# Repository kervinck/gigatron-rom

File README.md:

Software for Gigatron ROM
=========================

Important files
===============
```
gigatron-rom
 +--- LICENSE                   2-Clause BSD License
 +--- Makefile                  Marcel's Makefile
 +--- Core/                     Gigatron kernel and build tools
 |     +--- dev.asm.py          Development ROM (type 'make' to build):
 |     |                        Video/audio/io/kernel loops and cold storage
 |     |                        for applications and data ("kernel + ROM disk")
 |     +--- ROMv6.asm.py        Source for release ROM v6 (most recent release)
 |     `--- compilegcl.py       Stand-alone GCL to vCPU compiler (GT1 files)
 +--- interface.json            Formal bindings interface to ROM for programs
 +--- Apps/                     Built-in and example applications (GCL and GT1)
 |     +--- Blinky/Blinky.gcl   Very simple GCL program
 |     `--- HelloWorld/         Program that draws "Hello world" on screen
 +--- BASIC/                    Example BASIC programs
 +--- Utils/
 |     +--- BabelFish/          Generic Arduino sketch for talking with Gigatron
 |     +--- gt1dump.py          Dump or disassemble GT1 files
 |     +--- lcc/                LCC compiler with vCPU backend (NOT YET STABLE)
 |     `--- sendFile.py         Send GT1 or BASIC file from laptop/PC
 +--- Libs/                     C libraries for Gigatron programs
 |     `--- Example.c           Example C program
 +--- Docs/
 |     +--- GCL-language.txt    Gigatron Control Language and vCPU explanation
 |     +--- GT1-files.txt       vCPU object file format and ROM versioning
 |     +--- gtemu.c             Instruction set definition (as executable code)
 |     +--- vCPU-summary.txt    Overview of 16-bit virtual CPU instruction set
 |     `--- ...                 All on video, audio, native code, versioning...
 `--- Contrib/                  Contributions outside the kit's ROM and tooling:
       +--- at67/               BASIC compiler, emulator, 8-bit/16-bit
       |                        assembler/disassembler, debugger, MIDI music,
       |                        demos and games
       +--- Crouze/             TinyBASIC scripts (including graphclock.gtb)
       +--- Cwiiis/             Gigatris game
       +--- delpozzo/           VideoPoker game; Tools (CustomFish, sendFile)
       +--- dhkolf/             Fast emulator; Demos (SprPaint, PianoBeep,...)
       +--- docvolt/            Implementation on Sipeed Tang Nano 9K FPGA board
       +--- flok99/             Simple (and slow) visualizer using SDL2
       +--- gigawalt/           Walter's script
       +--- kervinck/           Ramblings (all work in progress)
       +--- makerspace48/       C examples, Prime.c and ASCII-mandelbrot.c
       +--- PhilThomas/         Javascript-based Gigatron emulator
       +--- pkupper/            Pluggy Reloaded's Babelfish (to be merged back)
       +--- tbraun-de/          Gigatron Mac; Python port of gtemu.c; maze.gt1
       +--- xopr/               NetTerm: Terminal program for SPI interface
       `--- xxxbxxx/            Bricks game; RPi port of BabelFish; frogstroll
```

Files generated by ROMv6.asm.py
===============================

See `Makefile` for how to make these.
```
ROMv6.lst                       Generated listing with disassembly, labels,
                                comments and source (large!)
ROMv6.rom                       ROM file for 27C1024 (PCB versions)
```

Memory map (RAM)
================
```
              0 1          53 54     127 128 129         (vSP)       255
             +-+-------------+-----------+-+-------------+--------------+
page 0       |0| System vars | User vars |1| User vars <-| Stack/Loader |
             +-+-------------+-----------+-+------+------+--+-----------+
page 1       | Video table                        | vReset  | Channel 1 |
             +------------------------------------+---------+-----------+ ---
page 2       |0                                239 240   249| Channel 2 |  ^
             |                                              +-----------+  |  Also see
page 3       |                                              | Channel 3 |  |  channelMask
             |                                              +-----------+  |
page 4       |            User vCPU code and/or data        | Channel 4 |  v
             |                                              +-----------+ ---
page 5-6     |                                               250     255|
             |                                                          |
             |                                               <- C stack |
             +----------------------------------------------------------+
page 7       | Sound tables                                             |
             +--------------------------------+-------------------------+
page 8-127   |0                            159|160                   255|
             | 120 lines of 160 pixels        |  Extra space for user   |
             | Default video memory           |  code and/or data       |
             =                                =                         =
             |                                |                         |
             +--------------------------------+-------------------------+
page 128-255 | - Gigatron 32K: mirrors pages 0-127                      |
             | - Gigatron 64K: additional 32KB or RAM                   |
	     | - Gigatron with RAM&IO expansion: banked memory          |
	     |   | bank 0       mirrors page 0-127                      |
             |   | banks 1,2.3  three additional banks of 32K RAM       |
             +----------------------------------------------------------+
              0                                                      255

[Note: In the next section, names in parentheses refer to *internal*
variables that are subject to change between ROM versions. See for a
more detailed explanation on compatibility the file Docs/GT1-files.txt]

Address   Name          Description
--------- ------------- -----------
0000      zeroConst     Constant value 0 (for arithmetic carry)
0001      memSize       Number of RAM pages detected at hard reset (64kB=0)
0002      (channel)     Sound channel update on current scanline
0003      (sample)      Accumulator for synthesizing next sound sample
0004      (reserved)    Reserved (Video extensions? MMU? v8808? ...?)
0005      (vCpuSelect)  Entry page of active interpreter (offset fixed to 255)
0006-0008 entropy       Randomness from SRAM boot and input, updated each frame
0009      videoY        Counts up from 0 to 238 in steps of 2 (odd in vBlank)
000a      (frameX)      Starting byte within page for pixel burst
000b      (frameY)      Page of current pixel row (updated by videoA)
000c      (nextVideo)   Jump offset to scan line handler (videoA, B, C...)
000d      (videoModeD)  Handler for every 4th line (pixel burst or vCPU)
000e      frameCount    Continuous video frame counter
000f      serialRaw     New raw serial read
0010      (serialLast)  Previous serial read (used for edge detection)
0011      buttonState   Edge-triggered and resettable input bits
0012      (resetTimer)  After 2 seconds of holding 'Start', do a soft reset
0013      (xout)        Memory cache for XOUT register
0014      xoutMask      The blinkenlights and sound on/off state
0015      (vTicks)      Remaining interpreter ticks (=units of 2 CPU cycles)
0016-0017 vPC           Interpreter program counter, points into RAM
0018-0019 vAC           Interpreter accumulator, 16-bits
0018      v6502_A       [v6502] Accumulator
0019      (v6502_BI)    [v6502] B Input Register (used by SBC)
001a-001b vLR           Return address, for returning after CALL
001a-001b v6502_PC      [v6502] Program Counter
001c      vSP           Stack pointer
001c      (v6502_S)     [v6502] Stack Pointer (kept as "S+1")
001d      (vTmp)        Scratch storage location for vCPU and v6502
001e      (vReturn)     Return address (L) from vCPU into the loop (H is fixed)
001f      (videoModeB)  ROMv2: Handler for every 2nd line (pixel burst or vCPU)
0020      (videoModeC)  ROMv2: Handler for every 3rd line (pixel burst or vCPU)
0021      romType       ROM v1:$1c v2:$20 v3:$28 v4:$38 v5a:0x40 v6:0x48 DEV:$f8
0021      channelMask   Low bits set active channels (x011->4, x001->2, x000->1)
0022-0023 sysFn         Address for SYS function call
0024-002b sysArgs       Arguments for SYS functions
0024      (v6502_ADL)   [v6502] Low Address Register
0025      (v6502_ADH)   [v6502] High Address Register
0026      (v6502_IR)    [v6502] Instruction Register
0027-0029 (v6502_P)     [v6502] Processor Status Register
002a      v6502_X       [v6502] Index Register X
002b      v6502_Y       [v6502] Index Register Y
002c      soundTimer    Countdown timer for playing sound
002d      (ledTimer)    Number of frames until next LED change
002e      ledState      Current LED state machine value (branch offset)
002f      ledTempo      Next value for ledTimer after LED state change
0030-007f userVars      Program variables (ROM<=v4)
0030-0035 (vIrqSave)    (v5+) vIRQ saved registers
0036-007f userVars_v5   Program variables (ROM v5)
0036-007f userVars_v6   Program variables (ROM v6)
0080      oneConst      Constant value 1 (for arithmetic carry)
0081-.... userVars2     More space for program variables
....-00ff <stack>       Call and value stack for vCPU (also used by ROM loader)
0100-01ef videoTable    Video indirection table (Y0,dX0,Y1,dX1,Y2,...,dX119)
01f0-01f5 vReset        vCPU routine to load and start Reset sequence
01f6-01f7 vIRQ_v5       (v5) Pointer to vCPU vIRQ handler
01f8      ctrlBits_v5   (v5) RAM and IO expansion control word
01f9      videoTop_v5   (v5) Blank top of screen. Must be even in [0..238].
01fa      wavA[1]       Sound channel 1: Waveform modulation with `adda'
01fb      wavX[1]       ...............: Waveform modulation with `xora'
01fc      keyL[1]       ...............: Frequency low 7 bits (bit7 == 0)
01fd      keyH[1]       ...............: Frequency high 8 bits
01fe      oscL[1]       ...............: Phase low 7 bits
01ff      oscH[1]       ...............: Phase high 8 bits
0200-02f9 userCode      vCPU code/data (default start of user code)
02fa      wavA[2]       Sound channel 2: Waveform modulation with `adda'
02fb      wavX[2]       ...............: Waveform modulation with `xora'
02fc      keyL[2]       ...............: Frequency low 7 bits (bit7 == 0)
02fd      keyH[2]       ...............: Frequency high 8 bits
02fe      oscL[2]       ...............: Phase low 7 bits
02ff      oscH[2]       ...............: Phase high 8 bits
0300-03f9 -             vCPU code/data
03fa      wavA[3]       Sound channel 3: Waveform modulation with `adda'
03fb      wavX[3]       ...............: Waveform modulation with `xora'
03fc      keyL[3]       ...............: Frequency low 7 bits (bit7 == 0)
03fd      keyH[3]       ...............: Frequency high 8 bits
03fe      oscL[3]       ...............: Phase low 7 bits
03ff      oscH[3]       ...............: Phase high 8 bits
0400-04f9 -             vCPU code/data
04fa      wavA[4]       Sound channel 4: Waveform modulation with `adda'
04fb      wavX[4]       ...............: Waveform modulation with `xora'
04fc      keyL[4]       ...............: Frequency low 7 bits (bit7 == 0)
04fd      keyH[4]       ...............: Frequency high 8 bits
04fe      oscL[4]       ...............: Phase low 7 bits
04ff      oscH[4]       ...............: Phase high 8 bits
0500-05ff -             vCPU code/data
0600-06ff -             vCPU code/data
0700-07ff soundTable    Interlaced waveforms (metal, triangle, pulse, sawtooth)
0800-7fff screenMemory  Default pages for screen memory
0800-089f -             Pixel line 0
08a0-08ff -             vCPU code/data
.........
7f00-7f9f -             Pixel line 119
7fa0-7fff -             vCPU code/data
--------- ------------- -----------
```

Memory map (ROM)
================
```
             +----------------------------------------------------------+  ---
$0000        | Boot and reset sequences                                 |   ^
             +----------------------------------------------------------+   |
$0100        | Video and audio loop (vertical blank lines)              |   |
             |                                                          |   |
$0200        | Video and audio loop (visible lines)                     |   |
             +----------------------------------------------------------+   |
$0300        | vCPU interpreter loop (primary page)                     |   |
             |                                                          |   |
$0400        | vCPU extended instructions (and some SYS functions)      |   |
             +----------------------------------------------------------+   |
$0500        | Shift tables                                             |   |
             |                                                          |   |  Core system
$0600        | SYS functions (LSRW and others)                          |   |  Kernel and drivers
             +----------------------------------------------------------+   |
$0700        | Font table (ASCII 32..81)                                |   |
             |                                                          |   |
$0800        | Font table (ASCII 82..126 and symbols 127-131)           |   |
             |                                                          |   |
$0900        | Notes table (C-0..A#7)                                   |   |
             |                                                          |   |
$0a00        | Inversion table                                          |   |
             +----------------------------------------------------------+   |
$0b00        | SYS functions (SendSerial, Sprites, SPI, ...)            |   |
             |                                                          |   |
$0d80-$11ff  | v6502 secondary interpreter                              |   |
             |                                                          |   |
$1200-$1241  | More proceesing during vertical blank lines              |   |
             |                                                          |   |
$1242-$14ff  | More SYS functions                                       |   |
             |                                                          |   v
             +==========================================================+  ---
             |                                                          |   ^
             | ROM tables: Embedded high-resolution images (packed)     |   |
             |                                                          |   |  Applications /
$1500-$ffff  | Include files: application-specific SYS functions        |   |  cold storage
             |                                                          |   |
             | ROM files: Embedded vCPU/v6502 applications (serialized) |   |
             |                                                          |   v
             +----------------------------------------------------------+  ---
              0                                                      255
```

SYS functions (ROM)
===================

```
Available since ROM v1:

00ad    SYS_Exec_88                     Load serialized vCPU code from ROM and execute
04a7    SYS_Random_34                   Get random number and update entropy
0600    SYS_LSRW1_48                    Shift right 1 bit
0619    SYS_LSRW2_52                    Shift right 2 bits
0636    SYS_LSRW3_52                    Shift right 3 bits
0652    SYS_LSRW4_50                    Shift right 4 bits
066d    SYS_LSRW5_50                    Shift right 5 bits
0687    SYS_LSRW6_48                    Shift right 6 bits
04b9    SYS_LSRW7_30                    Shift right 7 bits
04c6    SYS_LSRW8_24                    Shift right 8 bits
06a0    SYS_LSLW4_46                    Shift left 4 bits
04cd    SYS_LSLW8_24                    Shift left 8 bits
04e1    SYS_VDrawBits_134               Draw 8 vertical pixels
06c0    SYS_Unpack_56                   Unpack 3 bytes into 4 pixels
04d4    SYS_Draw4_30                    Copy 4 pixels to screen memory
00f4    SYS_Out_22                      Write byte to hardware OUT register
00f9    SYS_In_24                       Read byte from hardware IN port

Added in ROM v2:

0b00    SYS_SetMode_v2_80               Set video mode 0..3
0b03    SYS_SetMemory_v2_54             Set 1..256 bytes of memory to value

Added in ROM v3:

0b06    SYS_SendSerial1_v3_80           Send data out over game controller port
0c00    SYS_Sprite6_v3_64               Draw sprite of 6 pixels wide and N pixels high
0c40    SYS_Sprite6x_v3_64              Draw sprite mirrored in X direction
0c80    SYS_Sprite6y_v3_64              Draw sprite upside down
0cc0    SYS_Sprite6xy_v3_64             Draw sprite mirrored and upside down

Added in ROM v4:

0b09    SYS_ExpanderControl_v4_40       Set register in I/O and RAM expander
0b0c    SYS_Run6502_v4_80               Execute MOS 6502 code until BRK
0b0f    SYS_ResetWaveforms_v4_50        Setup sound tables in page 7
0b12    SYS_ShuffleNoise_v4_46          Shuffle noise table in page 7
0b15    SYS_SpiExchangeBytes_v4_134     Send and receive bytes

Added in ROM v5a:

00ef    SYS_ReadRomDir_v5_80            Navigate ROM directory

Added in ROM v6:

009e    SYS_Multiply_s16_v6_66          16 bits multiplication (from at67)
00a1    SYS_Divide_s16_v6_80            15 bits unsigned division (from at67)
00e6    SYS_ScanMemory_v6_50            Search byte in memory region
00e9    SYS_CopyMemory_v6_80            Copy memory region
00ec    SYS_CopyMemoryExt_v6_100        Copy memory across RAM extension banks
0b18    SYS_ReceiveSerial1_v6_32        Receive byte on input port (for the loader)

```

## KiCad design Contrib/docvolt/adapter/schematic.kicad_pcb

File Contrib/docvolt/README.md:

# Gigatron Running on FPGA
Verilog implementation of the Gigatron for the Tang Nano 9K FPGA board.

## Installation
Download and install the free *GOWIN EDA software* here: https://www.gowinsemi.com/en/support/download_eda (Prior registration is required)
The programmer is appropriate if you just want to flash the Tang Nano without making changes to the code. If you want to make changes, Gowin EDA is needed. The education version is sufficient there.

Notes: 
- The non-education version of the programs require a license. 
- There is an issue with Gowin Programmer V1.9.9.03. Use V1.9.9.02 instead. Later versions might also work.

## Flashing the Tang Nano
- Double-click the cell below "Operation" to open the Device configuration dialog.
- Select the bitstream file "gigatron.fs" and the flash initialization file "fpga_games.fi"

- Then save and click the "Configure/Program" button to write it all to the FPGA.

## Adapter Board
A VGA monitor, game controller and audio can be connected through the adapter board.

Find schematics and Gerber files of the adapter board here: [Schematic](schematic)

## Building the User Flash File From Source
The user flash file is basically the Gigatron's rom file, but in a format that's understood by the Gowin Programmer (ending: .fi). Unlike the gigatron's rom file which has a maximum size of 64K, the maximm size of the user flash file is 38K. This is due to the size of the embedded user flash of 608 KBit = 38K 16-bit words.
If you want to (re)build it, type "make games.rom" in a Linux command shell. I was using WSL/Ubuntu under Windows. Cygwin, MinGW, MSYS etc. do not work (at least not for me) 

## Youtube Video
More details in the video.

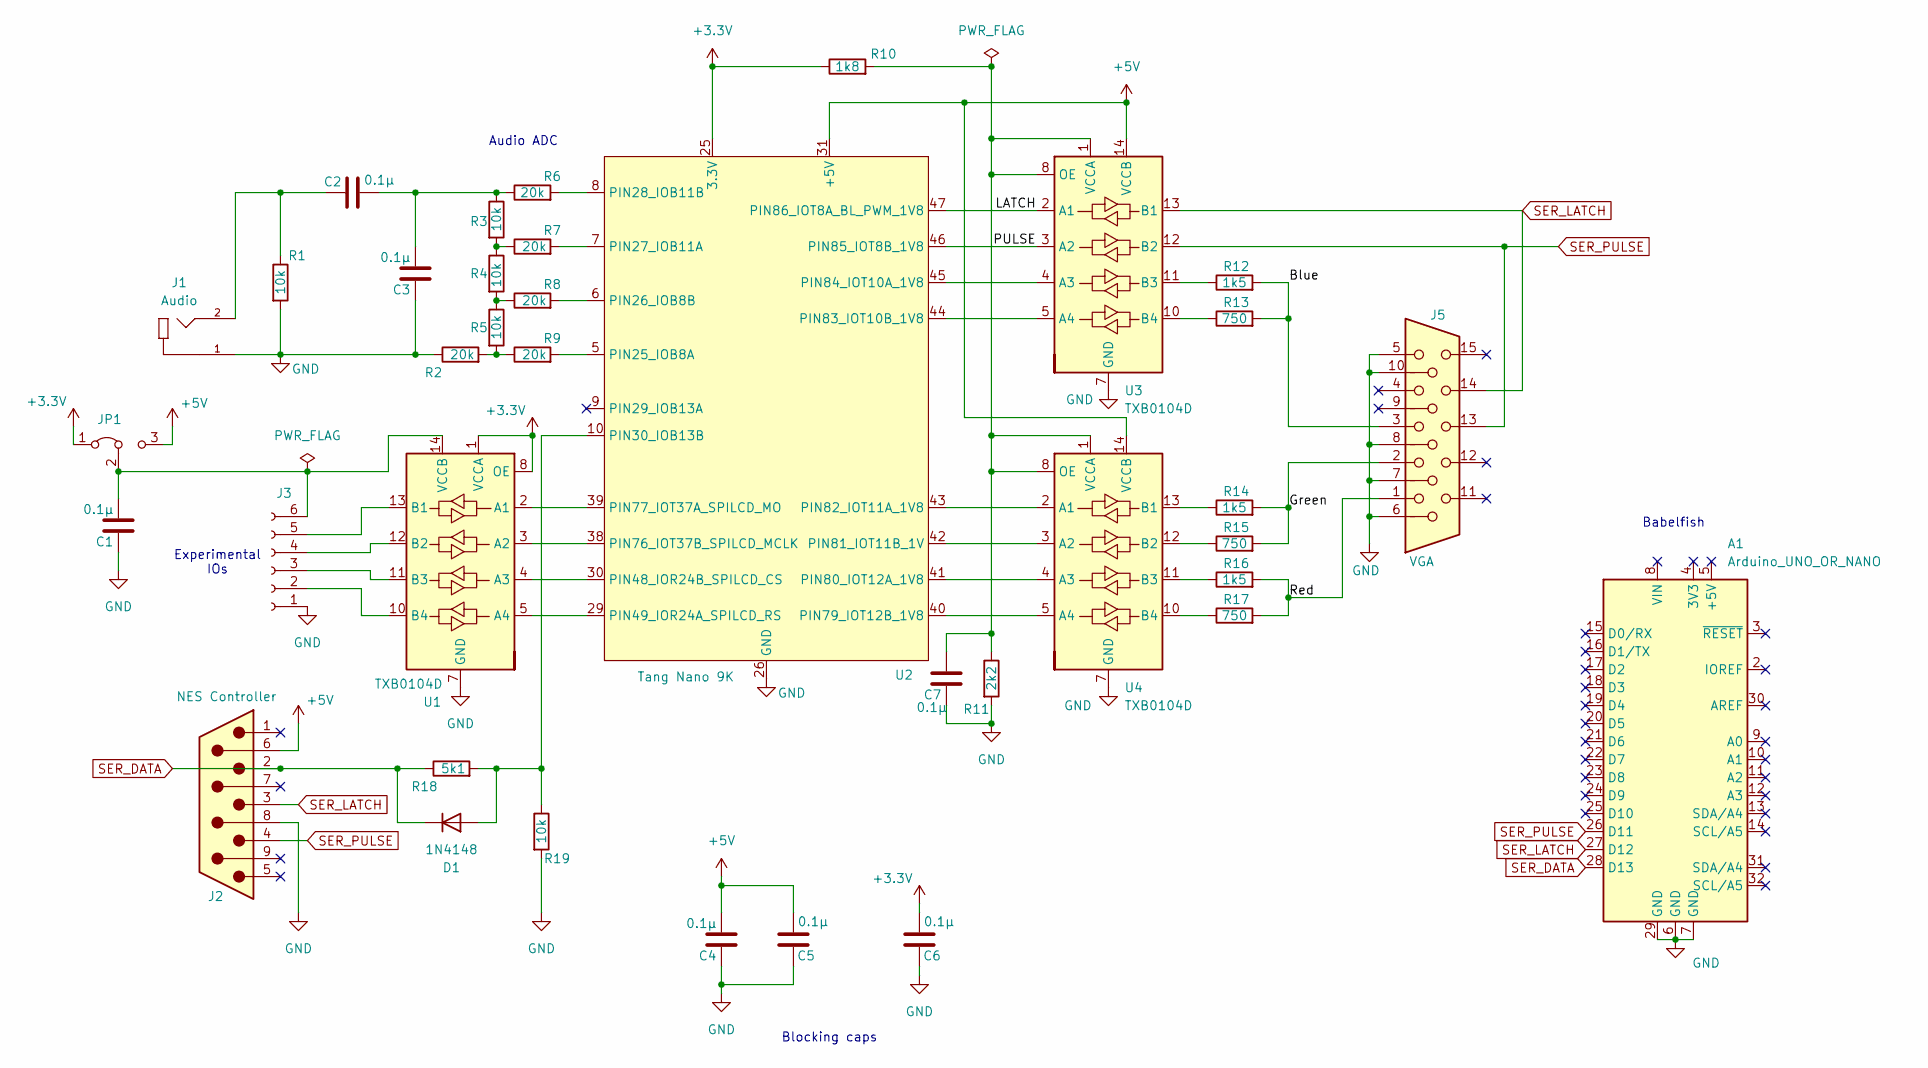
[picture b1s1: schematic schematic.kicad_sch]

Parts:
A1: Arduino_UNO_OR_NANO; Arduino_UNO_R3
C1, C2, C3, C4, C7: 0.1µ; C_Disc_D5.0mm_W2.5mm_P2.50mm
C5, C6: 0.1µ; C_1206_3216Metric_Pad1.33x1.80mm_HandSolder
D1: 1N4148; D_DO-35_SOD27_P7.62mm_Horizontal
J1: Audio; CUI_RCJ-041
J2: NES Controller; AMPHENOL_L717SDE09PA4CH4R
J3: Conn_01x06_Socket; PinSocket_1x06_P2.54mm_Vertical
J5: VGA; AMPHENOL_L77HDE15SD1CH4R
JP1: Jumper_3_Bridged12; Jumper
R1, R3, R4, R5, R19: 10k; R_Axial_DIN0207_L6.3mm_D2.5mm_P7.62mm_Horizontal
R2, R6, R7, R8, R9: 20k; R_Axial_DIN0207_L6.3mm_D2.5mm_P7.62mm_Horizontal
R10: 1k8; R_Axial_DIN0207_L6.3mm_D2.5mm_P7.62mm_Horizontal
R11: 2k2; R_Axial_DIN0207_L6.3mm_D2.5mm_P7.62mm_Horizontal
R12, R14, R16: 1k5; R_Axial_DIN0207_L6.3mm_D2.5mm_P7.62mm_Horizontal
R13, R15, R17: 750; R_Axial_DIN0207_L6.3mm_D2.5mm_P7.62mm_Horizontal
R18: 5k1; R_Axial_DIN0207_L6.3mm_D2.5mm_P7.62mm_Horizontal
U1, U3, U4: TXB0104D; SOIC-14_3.9x8.7mm_P1.27mm
U2: Tang Nano 9K; TangNano9k

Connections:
+3.3V: C6.2, JP1.1 (A), R10.1, U1.1 (VCCA), U1.8 (OE), U2.25 (3.3V)
+5V: C4.1, C5.2, J2.6, JP1.3 (B), U2.31 (+5V), U3.14 (VCCB), U4.14 (VCCB)
/Blue: J5.3, R12.2, R13.2
/DATA: A1.28 (D13), D1.1 (K), J2.2, R18.1
/Green: J5.2, R14.2, R15.2
/HSYNC: A1.26 (D11), J2.4, J5.13, U3.12 (B2)
/LATCH: U2.47 (PIN86_IOT8A_BL_PWM_1V8), U3.2 (A1)
/PULSE: U2.46 (PIN85_IOT8B_1V8), U3.3 (A2)
/Red: J5.1, R16.2, R17.2
/VSYNC: A1.27 (D12), J2.3, J5.14, U3.13 (B1)
GND: A1.6 (GND), A1.7 (GND), A1.29 (GND), C1.2, C3.2, C4.2, C5.1, C6.1, C7.2, J1.1, J2.8, J3.1, J5.5, J5.6, J5.7, J5.8, J5.10, R1.2, R2.1, R11.2, R19.2, U1.7 (GND), U2.26 (GND), U3.7 (GND), U4.7 (GND)
unnamed: C2.1, J1.2, R1.1
unnamed: C2.2, C3.1, R3.1, R6.1
unnamed: D1.2 (A), R18.2, R19.1, U2.10 (PIN30_IOB13B)
unnamed: J3.2, U1.10 (B4)
unnamed: J3.3, U1.11 (B3)
unnamed: J3.4, U1.12 (B2)
unnamed: J3.5, U1.13 (B1)
unnamed: C1.1, J3.6, JP1.2 (C), U1.14 (VCCB)
unnamed: R2.2, R5.2, R9.1
unnamed: R3.2, R4.1, R7.1
unnamed: R4.2, R5.1, R8.1
unnamed: U1.2 (A1), U2.39 (PIN77_IOT37A_SPILCD_MO)
unnamed: U1.3 (A2), U2.38 (PIN76_IOT37B_SPILCD_MCLK)
unnamed: U1.4 (A3), U2.30 (PIN48_IOR24B_SPILCD_CS)
unnamed: U1.5 (A4), U2.29 (PIN49_IOR24A_SPILCD_RS)
unnamed: R9.2, U2.5 (PIN25_IOB8A)
unnamed: R8.2, U2.6 (PIN26_IOB8B)
unnamed: R7.2, U2.7 (PIN27_IOB11A)
unnamed: R6.2, U2.8 (PIN28_IOB11B)
unnamed: U2.40 (PIN79_IOT12B_1V8), U4.5 (A4)
unnamed: U2.41 (PIN80_IOT12A_1V8), U4.4 (A3)
unnamed: U2.42 (PIN81_IOT11B_1V), U4.3 (A2)
unnamed: U2.43 (PIN82_IOT11A_1V8), U4.2 (A1)
unnamed: U2.44 (PIN83_IOT10B_1V8), U3.5 (A4)
unnamed: U2.45 (PIN84_IOT10A_1V8), U3.4 (A3)
unnamed: R12.1, U3.11 (B3)
unnamed: R13.1, U3.10 (B4)
unnamed: C7.1, R10.2, R11.1, U3.1 (VCCA), U3.8 (OE), U4.1 (VCCA), U4.8 (OE)
unnamed: R14.1, U4.13 (B1)
unnamed: R15.1, U4.12 (B2)
unnamed: R16.1, U4.11 (B3)
unnamed: R17.1, U4.10 (B4)

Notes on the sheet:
Audio ADC
Blocking caps
Experimental IOs
Babelfish

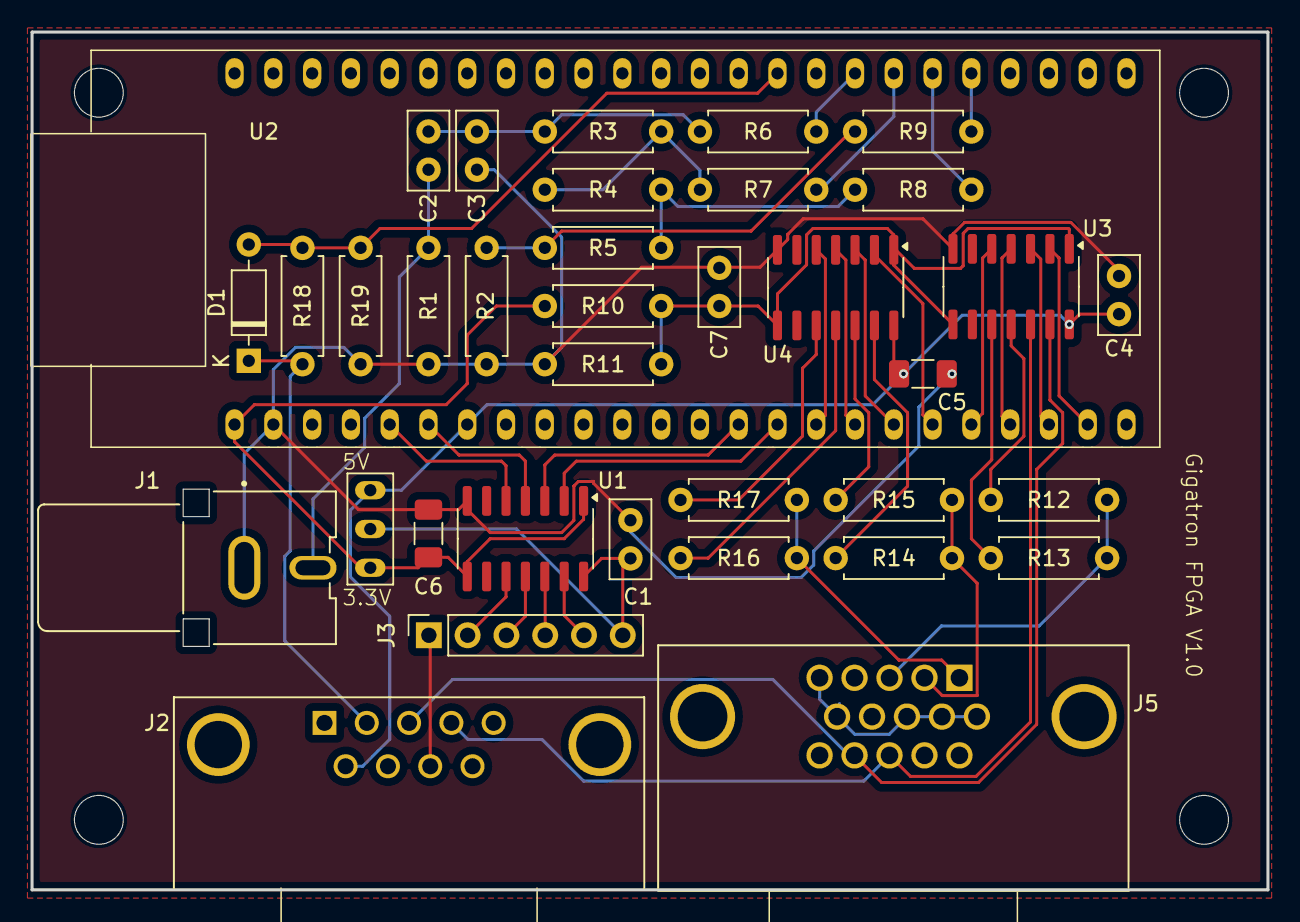
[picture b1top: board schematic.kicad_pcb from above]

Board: 2 copper layers, 80.9 x 56.2 mm, 36 parts (0 on the bottom side), 43 nets.

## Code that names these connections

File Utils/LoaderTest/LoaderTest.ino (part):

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// Uno     Name   OUT bit            CD4021     74HC595 (U39)    DB9 (J4)
// ------- ------ -------- --------- ---------- ---------------- --------
// Pin 13  PORTB5 None     SER_DATA  11 SER INP 14 SER           2
// Pin 12  PORTB4 7 vSync  SER_LATCH  0 PAR/SER None             3
// Pin 11  PORTB3 6 hSync  SER_PULSE 10 CLOCK   11 SRCLK 12 RCLK 4

#if ArduinoUno
 #define version "ArduinoUno"
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//                       +------+
//              ~RESET --|1.   8|-- Vcc
// PS/2 data       PB3 --|2    7|-- PB2  Serial data out
// PS/2 clock      PB4 --|3    6|-- PB1  Serial latch in
//                 GND --|4    5|-- PB0  Serial pulse in
//                       +------+
//                       ATtiny85

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void sendFirstByte(byte value)
{
  // Wait vertical sync NEGATIVE edge to sync with loader
  while (~PINB & (1<<SER_LATCH)) // Ensure vSync is HIGH first
    ;
  while (PINB & (1<<SER_LATCH)) // Then wait for vSync to drop
    ;

  // Send first bit
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  // Wait for bit transfer at horizontal sync POSITIVE edge.
  // This timing is tight for the first bit of the first byte and
  // the reason that interrupts must be disabled on the microcontroller.
  while (PINB & (1<<SER_PULSE))  // Ensure hSync is LOW first
    ;
  while (~PINB & (1<<SER_PULSE)) // Then wait for hSync to rise
    ;

  // Send remaining bits
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      PORTB &= ~(1<<SER_DATA);

    // Wait for bit transfer at horizontal sync POSITIVE edge.
    while (PINB & (1<<SER_PULSE))  // Ensure hSync is LOW first
      ;
    while (~PINB & (1<<SER_PULSE)) // Then wait for hSync to rise
      ;
  }
  checksum += value;
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
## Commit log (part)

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2020-04-10 Makefile: Rename Core/<rom>.py to Core/<rom>.asm.py
    For consistency with .vasm.py files, and for easier recognition.
2020-04-11 vasm.py: SYS operand compliancy
2020-04-22 Ver 0.8.23
    - Added the "%includePath" pre-processor command to the Assembler, (mainly for the BASIC compiler, but can be used by the user).
    - Fixed all the BASIC compiler samples so that generated *.gasm code is able to be assembled by the assembler separately, (required the "%includePath" command).
2020-04-24 Ver 0.8.23
    - Added auto configuration of 64K RAM for the emulator when loading 64K *.gbas, *.gasm, *.gcl and *.gt1 files, (configurable in "loader_config.ini").
    - Added code to reset the audio channel mask when loading files into the emulator.
    - Refactored operand handling within the BASIC compiler's optimiser.
2020-04-27 Ver 0.8.24
    - Added missing sprite image.
2020-04-29 Ver 0.8.25
    - Added the ASC() function to the BASIC compiler.
    - Added scrolling text to the Boing demo.
    - Fixed a bug in LEFT$, MID$ and RIGHTS that did not allow correct code generation when used in temporary expressions.
2020-05-04 Ver 0.8.27
    - Removed some temporary files.
2020-05-06 (git-fork-files) Saving: Core/dev.asm.py
2020-05-06 (git-fork-files) Saving: Core/Reset_v5.gcl
2020-05-06 interface.json: Add ROMv5a bindings
2020-05-07 Ver 0.9.0B, (Beta)
    - Removed cryptic pokes/peeks from examples and added a plethora of Gigatron and gtBASIC system variables accessible through the commands 'SET' and 'GET'.
    - Added an escape char '\' to allow gtBASIC strings to contain escape sequences, e.g. "\"TEST\"".
    - Added extra functionality to the validator that now allows it to check for optimised FOR loops spanning pages.
    - Added a not very well hidden easter egg example to the gtBASIC apps directory.
    - Hand created a few more fonts.
    - Fixed a rare bug that allowed page jumps to be inserted in between a POP and RET, POP and RET are now embedded within a %Return macro, (macros are indivisible).
2020-05-07 Ver 0.9.2B, (Beta)
    - Added the 'PSET' command to the BASIC compiler, uses the video indirection table to poke pixel addresses.
    - Added the 'POINT' command to the BASIC compiler, uses the video indirection table to peek pixel addresses.
    - Added two samples using PSET and POINT into the graphics examples directory.
    - Fixed the 'SET VIDEOTOP' command.
    - Added ROMv5a to the list of internal ROM's built into the emulator.
    - Added the -v option to gtMIDI, this allows you to create MIDI sequences with volume/velocity streams, (must match the -v option in miditones), use 'PLAY MIDIV' to playback the stream.
2020-05-09 Ver 0.9.3B, (Beta)
    - Testing Markdown Styles in README.md's.
2020-05-11 (git-fork-files) Creating: Apps/Loader/SYS_Loader_v4.py.forked
2020-05-11 Loader: Fix channelMask bug introduced in ROM v5a #88
    4-channel mode wasn't active after loading.
    The root causeh is the rewrite of 35ef40a55e6407f58811f923e5600680139bebc2
    (Loader: Improve channelMask handling #88)
    Although the address logic for detecting channel overwrites is
    correct, we wrongly apply it to the last fragment that BabelFish
    sends. Only in this last fragment N=0 and the sent address is the
2020-05-15 Ver 0.9.5B, (Beta)
    - Added a bunch of transcendental functions to the vASM assembler and BASIC compiler expression handlers.
    - Added multi dimensional arrays to 16it integers, (up to 3 dimensions).
    - Added the ASM and ENDASM keywords to the BASIC compiler, you can now easily embed vASM code in BASIC code.
    - Added a simple example that shows how to inject vASM code into BASIC using the ASM and ENDASM keywords; 'Notes.gbas" in the audio examples directory.
    - Added the DOWNTO keyword to the FOR NEXT syntax, this allows more oppurtunities for optimisations and better control to the user.
    - Removed the auto step logic from FOR NEXT loops and gave explicit control to the user through DOWNTO.
2020-05-18 Ver 0.9.6B, (Beta)
    - Fixed a couple of warnings for Linux/gcc.
2020-06-06 Ver 0.9.9B, (Beta)
    - Added 'BCDADD', 'BCDSUB' and 'BCDINT' to the BASIC compiler; these commands provide basic arithmetic for unpacked BCD, (one digit per byte), of any length, (until you run out of RAM). Great for sco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
    - Added an overlap option to sprites, this allows sprites to be drawn with widths that are NOT a multiple of six. The artist is required to allow for the overlap when generating sprite images.
    - Added the 'POLYR' keyword, this is a relative coord system version of 'POLY' that allows for offsets and symmetry flipping in the X and Y directrons. Great for generating symmetrical and instanced 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
    - Added byte arrays to the
2020-06-22 Ver 1.0.0B, (Beta)
    - Warning fixes for Linux/Max gcc.
2020-06-29 Checkpoint: Remove copied files
2020-12-26 Added prime number example
2020-12-26 Moved .c examples to Apps
    Moved .c examples and compiled .gt1 files from Lib to Apps folder.
2021-01-07 Ver 1.0.6R, (Release)
    - Added missing resource files.
2021-01-08 Add sendFile.py
2021-01-08 Add VideoPoker files
2021-01-10 Ver 1.0.6R, (Release)
    - Added simple version control to the runtime, runtimes must now exactly match what the compiler expects, (defined in runtime/util.i and assembler.h). The current runtime as of this release is 0100, 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
    - Added value handling to %define, defines can now be any value that int16_t supports, not just on or off.
    - Removed some code duplication from linker.cpp that was duplicating some of the %define functionality in assembler.cpp
    - Changed the top left hand flashing pixel error message for incorrect ROM versions to center pixel flashing, it is more noticable now and won't be h
2021-01-13 Ver 1.0.7R, (Release, runtime 0101)
    - Added the 'LOAD MIDI' command to the gtBASIC compiler, currently supports gtMID binary format MIDI files created by the gtMIDI tool.
    - Added the 'TCLIP <ON/OFF>' command to the gtBASIC compiler, this enables/disables text clipping when printing; useful for printing into offscreen areas, (use with caution).
    - Added an experimental pragma '_enable6BitAudioEmu_ <ON/OFF>' to the gtBASIC compiler, this enables/disables full 6bit audio for ROM's >= ROMv5a, (currently experimental and emulation only).
    - Added a MIDI player/visualiser to the Audio Editor, (CTRL+A), this allows you to play .gtMID files and experiment with 4bit and 6bit qualities, see the res/audi
2021-01-15 Ver 1.0.7R, (Release, runtime 0101)
    - Made Release the default build option for both MSVC and gcc.
2021-01-16 Ver 1.0.7R, (Release, runtime 0103)
    - Added better error handling to PRAGMAS
    - Added better error handling to PRAGMA parameters
    - Added better error handling to compound statements, e.g. 'CONST DIM', 'ON GOTO', etc
    - Refactored and reformatted error output into a more standardised format, i.e. 'NAMESPACE::FUNCTION : MODULE:LINE_NUMBER : <OPTIONAL ERROR> : BASIC_SOURCE_LINE'
    - Fixed a few sample programs that contained syntax errors that were being ignored.
2021-01-25 Ver 1.0.9R, (Release, runtime 0104)
    - Fixed a nasty lazy unsigned cast bug that should have been an explicit check in Operators::handleDualOp(); this was only causing issues on the Rasberry Pi 400...
2021-02-03 Implement Marcel's 128K RAM and IO extension board.
2021-02-05 Ver 1.0.9R, (Release, runtime 0104)
    - Fixed a uint8_t overflow issue in Loader::saveGt1File().
2021-02-05 Ver 1.0.9R, (Release, runtime 0104)
    - Fixed a bug where the emulator was not switching to the correct memory model if the symbol 64k was missing from a 64k .gt1 file's name.
    - Removed superfluous calls to Memory::initialise().
2021-05-04 Tidy up in the hope of making it useful.
    In particular this adds a setuptools setup.py script,
    and instructions on how to use it.
    It's not ideal.
    I've also fixed up the build script somewhat.
2021-05-07 Add .eggs directory to py-gtemu ignores
2021-05-12 Create empty project.
    Is this the best version of the buildscript ever?
2021-05-12 Fix a few bugs with one byte instructions and add new features.
    Some of the one byte instructions had a few issues, mostly related
    to the fact that 1 entry tuples should be defined with a comma
    at the end such as (0xad,) instead of (0xad).
    In addition, functions to assemble the experimental instructions
    CALLI, CMPHS, and CMPHU we added to the assembler.
    Furthermore, this patch introduces a few callbacks that can greatly
2021-05-13 Import the right-shift table from the main project
    This is going to be needed later...
2021-05-21 Fix source encoding issues in asm.py
    The enableListing() function reads the source code of the assembler
    script. However it didn't follow the rules that Python follows to
    detect the encoding.
    When writing the listing file, we should probably use utf-8.
2021-05-21 NFC Import ROMv5a.asm.py as sys/ROM.asm.py
    I'm going to make a SYS function!
2021-05-21 Importing Mandelbrot_v1.gcl as Mandelbrot.gcl
    I intend to port this to use my new SYS function.
2021-05-30 SYS_CopyMemory_DEVROM_80, SYS_CopyMemoryExt_DEVROM_94
2021-06-03 Mention the multiply work in the py-gtemu README.
2021-09-03 Added SYS_ScanMemory_DEVROM_50
2021-09-30 Simulate gal-based variant of io&ram expansion board
2021-09-30 reselecting the card should return to cmd state
2021-09-30 Tidy up step_vcpu() and run_vcpu_to()
    This may provide a speedup when benchmarking.
2021-09-30 Bump version
2021-10-07 Fixes to spi emulation
2021-10-09 Tweaks based on stall profile.
    Down to 6:36 - 33.3% of the original.
    The changes make basically no difference, only a few seconds!
    They are optimising the wrong thing!
    Stall is not the problem, it's a small proportion of the cost.
    The major cost is the display loop,
    which I guess is proportional to exectution time + stall.
2021-10-14 romType for ROMv5a should be 0x40, not 0xf8 like the dev rom.
2021-10-20 Update Mandelbrot to use Karatsuba's algorithm
    6:56 - 35.0% of the original.
    This actually makes things a bit slower than the previous version,
    but it's faster than before stall-profiling and optimisation.
    Hopefully another round of profiling and optimisation will improve this
    too.
    Running Original
2021-10-27 Vastly improved CardBoot. Apps/CardTest becomes Apps/CardBoot.
2021-10-28 CardBoot: better behavior with invalid drives
2021-11-15 Fix hardcoded addresses in Browser_SDCard - Introduce public call SYS_ReceiveSerialByte_DEVROM_32 - Browser has more cases for SYS_NextByteIn, with devrom defaulting on public version - Copy to hw/Br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
2022-01-13 Fixed command parsing bug
2022-01-20 Added SYS_OsCall
2022-01-24 Restored bindings.h into Contrib\kervinck\gcl
2022-01-31 Create veekooFIN
2022-02-14 Hack Browser_SDCard_ROMv2_v1.gbas to fit in Pro Micro memory
2022-02-21 Rename multiplication.py to quarter-square.py
    I'm going to try a different approach.
2022-04-14 Implement half-square multiplication
    Takes 119 cycles.
    Could be made slightly cheaper by using one more variable.
2022-05-20 Added SYS_ScanMemoryExt
2022-05-20 Reset.gcl: improved memory detection. changed chord.
2022-08-25 Gigatron graph paper
    This postscript program will output a 160 x 120 grid on A4 paper.
    The output is landscape,
    and is marked with the default addresses of the Gigatron display.
    It goes to some lengths to get good output
    by using the device space units for the grid.
    Getting the dashed lines right was a total pain!
2022-09-09 Updated sd image in gtemu for new cardboot/system.gt1
2022-10-14 Updated glcc to GLCC_RELEASE_1.5-15-g21ad078
2022-11-01 Add minipro instructions (linux)
2022-11-03 Racer: car crash noise (engine sound changed as well)
2022-11-21 Unified vRTI. Defined userVars_vX, ctrlBits_v5
2022-11-21 Updated gtbasic to avoid using $30-35 when using vIRQ
2022-11-26 Fixed unified vRTI timing mismatch
2022-12-07 Update/correct v5 todo list
2023-07-14 Removed Tetronis. Added GtMine
2023-07-18 Added define -DWITH_SPI_BITS to control the SPI bitmask.
    Variable WITH_SPI_BITS defines the number of potential MISO bits in
    bytes returned by a RAM&IO expansion board (in range 1 to 4). The
    GAL-based expansion boards work will all four settings. Marcel's
    original board theoretically offers four spi channels but in
    practice supports only one connected device on one of the first
    WITH_SPI_BITS channels. Hans61 7400-based board with two channels
2023-07-18 Created ROMv6 and new dev.rom
2023-11-09 Updated README and Docs for ROMv6
2024-04-30 initial checkin for simulation files
2024-05-19 FPGA implementation
2024-06-06 Added and populated Contrib/lb3361
2024-06-24 fpga: add simple input and audio (nexys only), audio not perfect, added custom rom mostly with games that will work with fpga board buttons simulation: added proper reset and input switches missles: 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
2024-12-11 Updated GLCC to GLCC_RELEASE-2.5
